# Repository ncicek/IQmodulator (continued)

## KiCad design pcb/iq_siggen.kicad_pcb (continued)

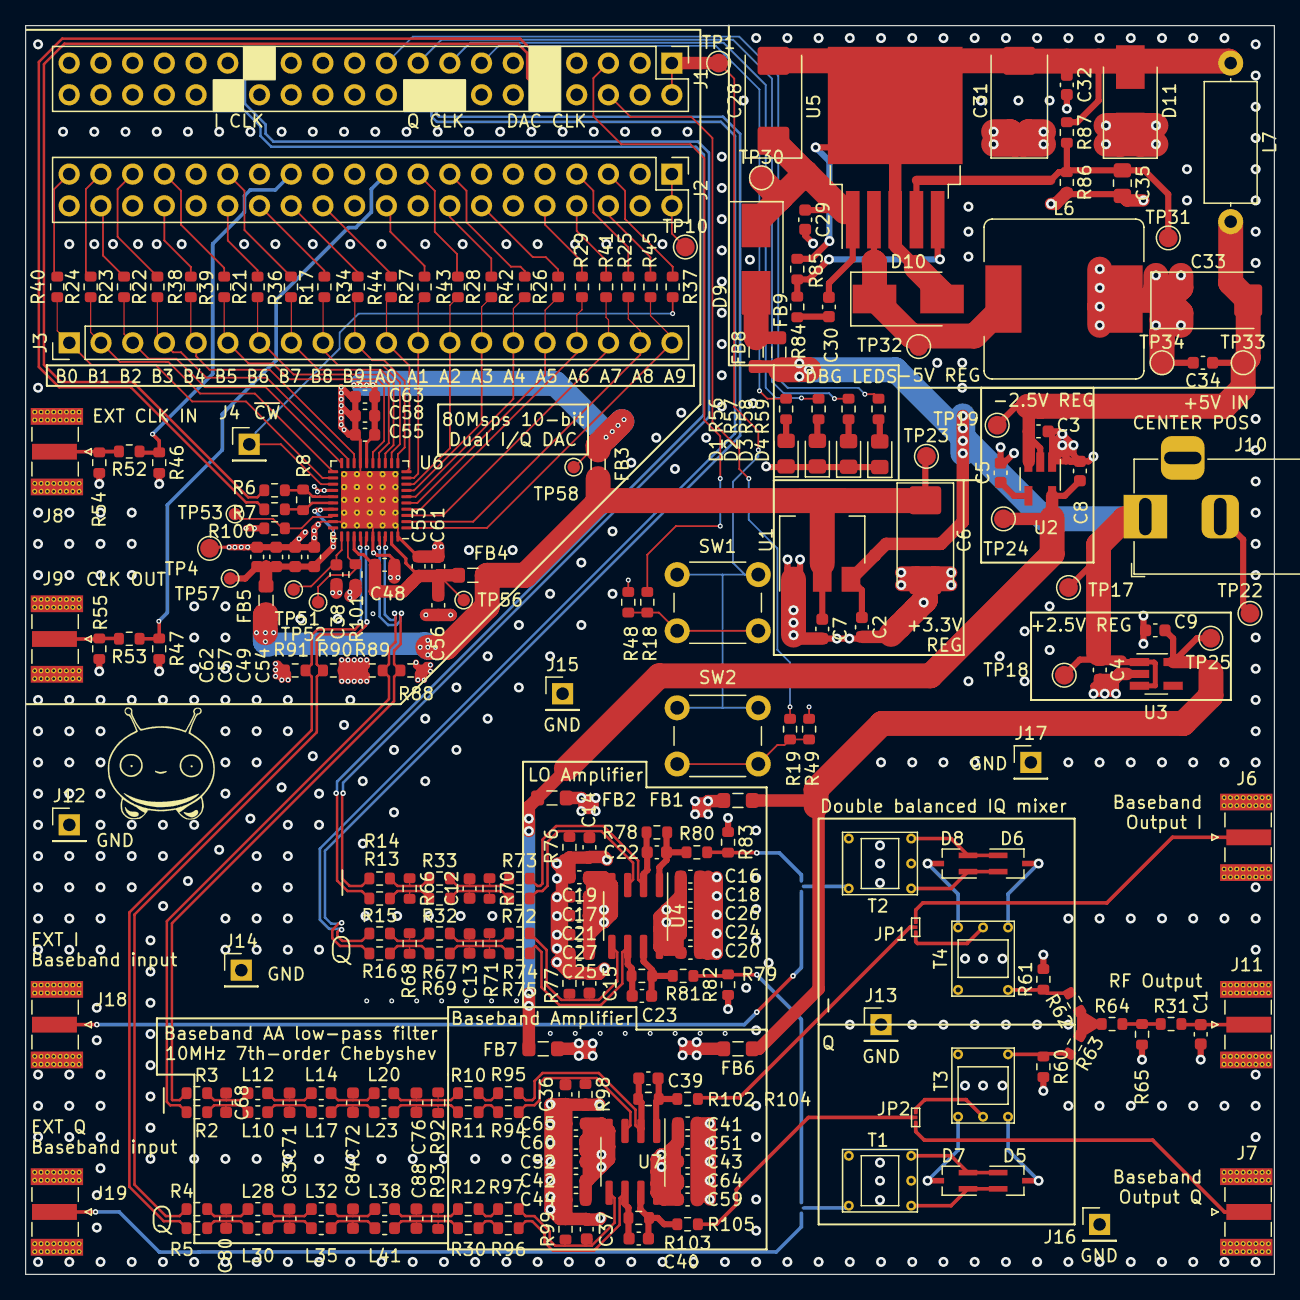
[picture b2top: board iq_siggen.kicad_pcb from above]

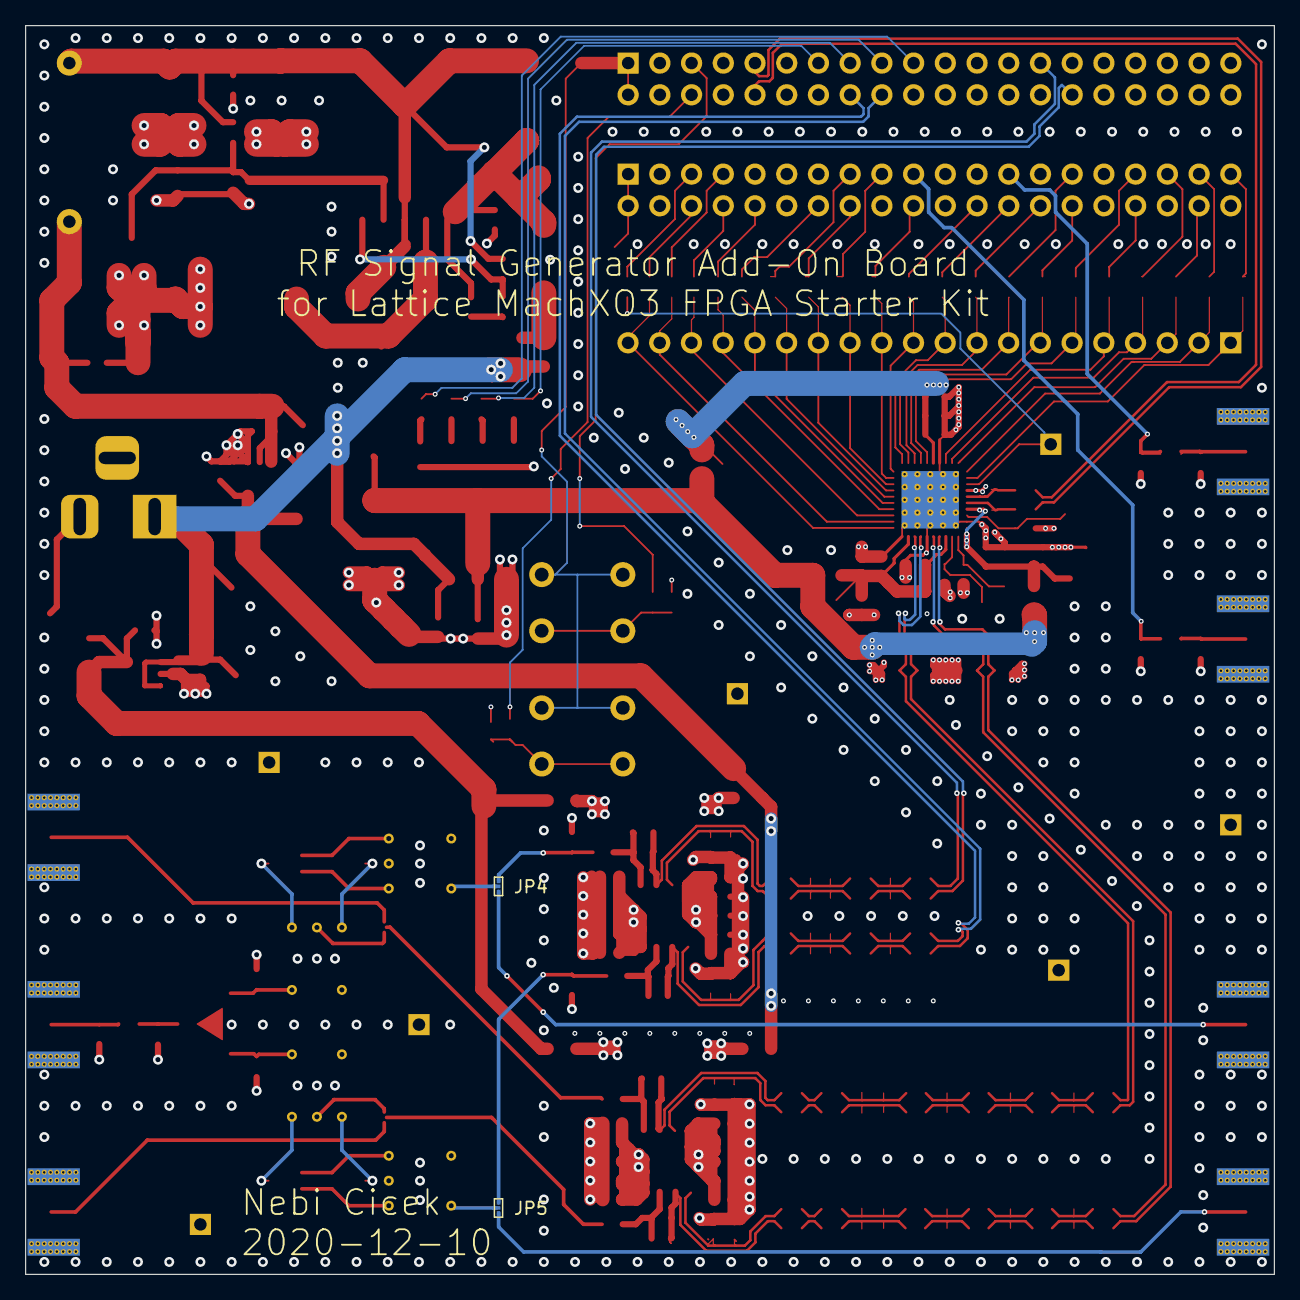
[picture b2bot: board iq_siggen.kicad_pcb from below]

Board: 4 copper layers, 100.0 x 100.0 mm, 256 parts (2 on the bottom side), 161 nets.

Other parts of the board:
C80, C88: 330p; C_0603_1608Metric
C83, C84: 680p; C_0603_1608Metric
L28, L30, L38, L41: 330n; L_0603_1608Metric
L32, L35: 470n; L_0603_1608Metric

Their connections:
/IQ DAC and AA filter/Q AA filter/50R_IN_N: C80.2, L30.1; also elsewhere on the board
/IQ DAC and AA filter/Q AA filter/50R_IN_P: C80.1, L28.1; also elsewhere on the board
/IQ DAC and AA filter/Q AA filter/50R_OUT_N: C88.2, L41.2; also elsewhere on the board
/IQ DAC and AA filter/Q AA filter/50R_OUT_P: C88.1, L38.2; also elsewhere on the board
/IQ DAC and AA filter/Q AA filter/F2_N: C84.2, L35.2, L41.1
/IQ DAC and AA filter/Q AA filter/F2_P: C84.1, L32.2, L38.1
/IQ DAC and AA filter/Q AA filter/F_N: C83.2, L30.2, L35.1
/IQ DAC and AA filter/Q AA filter/F_P: C83.1, L28.2, L32.1

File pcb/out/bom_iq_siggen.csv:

Comment,Designator,Footprint,LCSC Part Number
3p,C1,Capacitor_SMD:C_0603_1608Metric,
DNI,"C12,C13",Capacitor_SMD:C_0603_1608Metric,
0.1u,"C16,C17,C18,C19,C20,C21,C30,C38,C41,C42,C43,C44,C48,C49,C51,C52,C53,C54,C55,C56,C57,C58",Capacitor_SMD:C_0603_1608Metric,C14663
4.7p,"C14,C15,C22,C23,C36,C37,C39,C40",Capacitor_SMD:C_0603_1608Metric,C1669
220u 25V tantalum,C28,Capacitor_Tantalum_SMD:CP_EIA-7343-43_Kemet-X_Pad2.25x2.55mm_HandSolder,C7231
220u tantalum 25V,"C31,C33",Capacitor_Tantalum_SMD:CP_EIA-7343-43_Kemet-X_Pad2.25x2.55mm_HandSolder,C7231
DNI - Feedforward cap,C35,Capacitor_SMD:C_0805_2012Metric_Pad1.15x1.40mm_HandSolder,
10n,C5,Capacitor_SMD:C_0603_1608Metric,C57112
220u,C6,Capacitor_Tantalum_SMD:CP_EIA-7343-43_Kemet-X_Pad2.25x2.55mm_HandSolder,C7231
680p,"C71,C72,C83,C84",Capacitor_SMD:C_0603_1608Metric,C30816
330p,"C68,C76,C80,C88",Capacitor_SMD:C_0603_1608Metric,C1664
10u,"C2,C3,C4,C7,C8,C9,C24,C25,C26,C27,C29,C32,C34,C59,C60,C61,C62,C63,C64,C65",Capacitor_SMD:C_0603_1608Metric,C19702
LED,"D1,D2,D3,D4",LED_SMD:LED_0805_2012Metric_Pad1.15x1.40mm_HandSolder,C34499 
BAT15-04W,"D5,D6,D7,D8",Package_TO_SOT_SMD:SOT-323_SC-70_Handsoldering,
MBRS540T3G,"D9,D10,D11",Diode_SMD:D_SMB_Handsoldering,C14651
Ferrite_Bead_Small,"FB1,FB2,FB3,FB4,FB5,FB6,FB7,FB8,FB9",Inductor_SMD:L_0805_2012Metric_Pad1.05x1.20mm_HandSolder,C19330
J3 - BANK0,J1,Connector_PinHeader_2.54mm:PinHeader_2x20_P2.54mm_Vertical,
Barrel_Jack,J10,Connector_BarrelJack:BarrelJack_Horizontal,
Conn_Coaxial,"J6,J7,J8,J9,J11,J18,J19",iq_siggen:SMA_Samtec_SMA-J-P-X-ST-EM1_EdgeMount_withSTEP,
Conn_01x01_Male,"J4,J12,J13,J14,J15,J16,J17",Connector_PinHeader_2.54mm:PinHeader_1x01_P2.54mm_Vertical,
J4 - BANK1,J2,Connector_PinHeader_2.54mm:PinHeader_2x20_P2.54mm_Vertical,
Conn_01x20_Male,J3,Connector_PinHeader_2.54mm:PinHeader_1x20_P2.54mm_Vertical,
SolderJumper_3_Open,"JP1,JP2,JP4,JP5",iq_siggen:50ohm_solder_jumper,
330n,"L10,L12,L20,L23,L28,L30,L38,L41",Inductor_SMD:L_0603_1608Metric,C46859
470n,"L14,L17,L32,L35",Inductor_SMD:L_0603_1608Metric,C21307
33u,L6,Inductor_SMD:L_Bourns_SRR1260,
3.3u,L7,Inductor_THT:L_Axial_L9.5mm_D4.0mm_P12.70mm_Horizontal_Fastron_SMCC,
6.8k - optional output termination,R100,Resistor_SMD:R_0603_1608Metric,
1.985k,R101,Resistor_SMD:R_0603_1608Metric,
22,"R17,R18,R19,R21,R22,R23,R24,R25,R26,R27,R28,R29,R34,R36,R37,R38,R39,R40,R41,R42,R43,R44,R45,R52,R53",Resistor_SMD:R_0603_1608Metric,C23345
3k,"R48,R49,R86",Resistor_SMD:R_0603_1608Metric,C4211
DNI,"R46,R47,R54,R55,R66,R68",Resistor_SMD:R_0603_1608Metric,
220,"R56,R57,R58,R59",Resistor_SMD:R_0603_1608Metric,C22962
0,"R2,R3,R4,R5,R6,R7,R10,R11,R12,R13,R14,R15,R16,R30,R31,R32,R33,R67,R69",Resistor_SMD:R_0603_1608Metric,C21189
16.5,"R62,R63,R64",Resistor_SMD:R_0603_1608Metric,C12054
DNI-50,"R60,R61,R65,R82",Resistor_SMD:R_0603_1608Metric,
499,"R72,R73,R74,R75,R94,R95,R96,R97",Resistor_SMD:R_0603_1608Metric,C23065
1.5k,"R76,R77,R78,R79",Resistor_SMD:R_0603_1608Metric,C22843
100,"R8,R70,R71",Resistor_SMD:R_0603_1608Metric,C22775
49.9,"R80,R81,R92,R93,R104,R105",Resistor_SMD:R_0603_1608Metric,C23185
DNI - 50,R83,Resistor_SMD:R_0603_1608Metric,
47k,"R84,R85",Resistor_SMD:R_0603_1608Metric,C25819
1k,"R87,R98,R99,R102,R103",Resistor_SMD:R_0603_1608Metric,C21190
24.9,"R88,R89,R90,R91",Resistor_SMD:R_0603_1608Metric,C22916
SW_Push,"SW1,SW2",Button_Switch_THT:SW_PUSH_6mm_H5mm,
Transformer_1P_SS,"T1,T2,T3,T4",iq_siggen:trifilar_wound_toroidal_rf_transformer,
TestPoint,"TP1,TP4,TP10,TP17,TP18,TP19,TP22,TP23,TP24,TP25,TP30,TP31,TP32,TP33,TP34",TestPoint:TestPoint_Pad_D1.5mm,
TestPoint,"TP51,TP52,TP53,TP56,TP57,TP58",TestPoint:TestPoint_Pad_D1.0mm,
AMS1117-3.3,U1,Package_TO_SOT_SMD:SOT-223-3_TabPin2,C6186
TPS72325DBVR,U2,Package_TO_SOT_SMD:SOT-23-5_HandSoldering,C69932
TLV73325PDBVT,U3,Package_TO_SOT_SMD:SOT-23-5_HandSoldering,
TLV3542IDR,"U4,U7",Package_SO:SOIC-8_3.9x4.9mm_P1.27mm,
LM2596S-ADJ,U5,Package_TO_SOT_SMD:TO-263-5_TabPin3,
MAX5853ETL-T,U6,iq_siggen:qfn_max5853,

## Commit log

2020-09-22 Verilator linting
2020-09-22 remove old file
2020-09-22 move to wishbone architecture
2020-09-27 remove idle transmission
2020-09-27 remove default nonetype net to make lattice reveal work
2020-09-27 drop the old top verilog file
2020-09-27 uart comms script now working
2020-09-27 fix sinewave harmonics due to bad table
2020-09-27 improve modulation amount so it can go down to zero
2020-09-27 add cocotb + jupyter dds output spectral harmonic analyzer
2020-11-14 Add PCB
2020-11-14 clean up
2020-11-14 clean up 2
2020-11-14 rtl updates
2020-11-14 add python register access script
2020-11-14 sims and dco spectral purity analysis
2020-11-14 add gnu radio experimentation
2020-11-14 s params for a mixer coil that i wound
2020-11-15 update dds to output quadrature sines
2020-11-15 iq generation rtl initial commit
2020-11-15 update spectral analysis data
2020-11-17 Define pin map, clean up schematic
2020-11-17 kicad junk in gitignore
2020-11-17 add iq output to dds and to fm gen
2020-11-17 update sine table generator script for bit width issue (include sign bit)
2020-11-17 add gnu radio sims
2020-11-17 update hex files and fm gen sim
2020-11-18 clean up ERC, more DFT stuff, started sigma delta adc
2020-11-18 add ext LO connectors, more decoupling
2020-11-19 started assigning footprints
2020-11-20 add schematic libs
2020-11-20 Update footprints, move to 0603 passives for JLCPCB assembly, create transformer footprints
2020-11-21 add design rules, import parts
2020-11-21 routing mixer
2020-11-21 lined up data bus resistors, done 5v reg, started the -5V switching regulator
2020-11-22 finish up vregs, routed filters, iq baseband outputs
2020-11-23 layout progress
2020-11-25 Add SMA step model
2020-11-25 route A and B channels on input connector
2020-11-26 LO amp routing
2020-11-27 clean up LO driver routing
2020-11-28 clean up baseband amplifier routing, make it like the LO amp
2020-11-28 route power for amplifiers, fill zones for gnd and amplifiers
2020-11-28 routing the dac wires
2020-11-30 laying out split gnd pours
2020-12-02 routing contiued, add swtiches, remove test points, all parts now positioned on board
2020-12-05 layout refininements, stitching vias
2020-12-06 clean up designators on silkscreen, label connectors and circuit blocks
2020-12-10 clean up, label sub circuit blocks in silkscreen document the expected clock and baseband amplitudes based on opamp gains
2020-12-10 update the solder jumper clearance
2020-12-10 update top level for 10 bit per channel output
2020-12-11 populate LCSC BOM for JLCPCB assembly
2020-12-11 clean
2020-12-11 update ignore file
2020-12-11 add second parallel ferrite bead for input of negative 5V generator
2020-12-11 fill out more components in BOM with LCSC parts
2020-12-11 final touches
2020-12-11 add output gerbers
2020-12-11 add multisim filter simulation
2020-12-25 Move rf board into it's own folder
2020-12-25 mend
2020-12-25 Sigma delta adc PCB initial commit
2020-12-26 mostly done layout
2020-12-26 finish the board
2021-01-14 add lattice project folder
2021-01-14 add phase shifter block
2021-01-14 add impl folder
2021-01-14 update project file, fix plls, meet timing
2021-01-14 rename sys clock pll drive dac_clk
2021-02-03 update rc network values after tuning
2021-02-06 add some untracked files
2021-02-07 add dac support
2021-02-07 switch to verilator
2021-02-07 fix dac config mode bug, ignore some linter warnings
2021-02-07 add delay to cw pin to meet timing for dac latch
2021-02-07 fix timing of dac init
2021-02-07 baseband dac is now working
2021-02-07 Add setup/hold time constraints for DAC
2021-02-07 switch to multiplier for modulation amount scaling
2021-02-08 update uart script
2021-02-08 update modulation multplier
2021-02-08 update tb reset button
2021-02-08 add more timing margin to dac output constraints
2021-02-10 remove iq_gen
2021-02-10 fix up the modulation multiplier, register outputs to dac
2021-02-10 clean up lattice project folder
2021-02-10 update timing preferences
2021-04-11 Add baseband gain control, LO improvements
2021-05-30 Create LICENSE
2021-05-30 Add some documentation and photos
2021-05-30 Update README.md
    Fix link
2023-04-05 Add verilog-ethernet submodule
2023-04-05 Add MII to RMII converter submodule
